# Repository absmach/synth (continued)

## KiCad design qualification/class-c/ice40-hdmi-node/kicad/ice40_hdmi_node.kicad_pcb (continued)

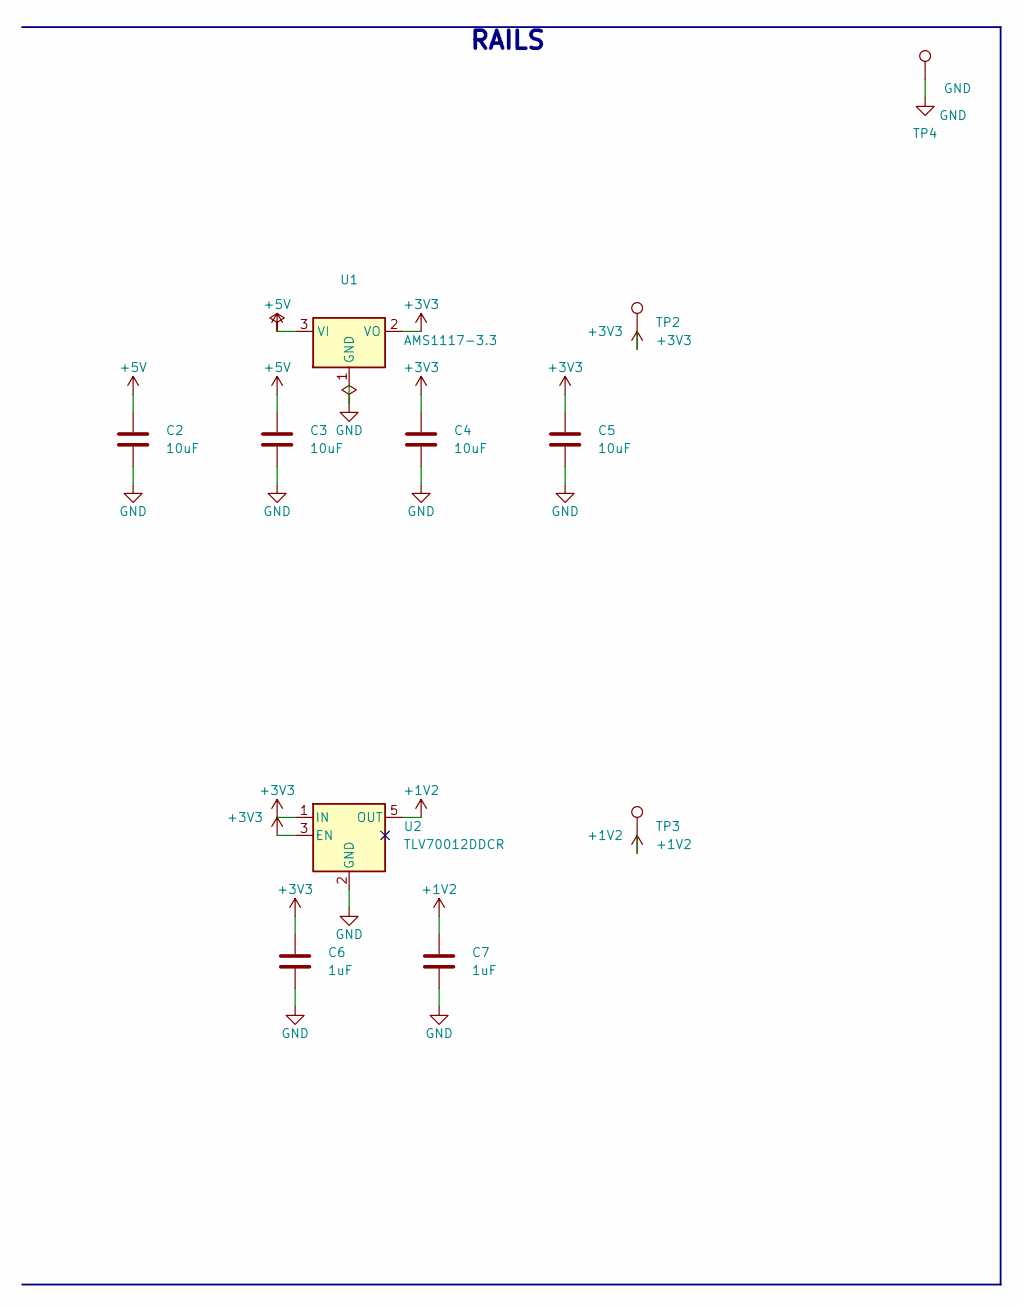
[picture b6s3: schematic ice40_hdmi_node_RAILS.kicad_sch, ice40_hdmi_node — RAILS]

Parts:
C2, C3, C4, C5: 10uF; C_0805_2012Metric
C6, C7: 1uF; C_0603_1608Metric
TP2: +3V3; TestPoint_Pad_D1.5mm
TP3: +1V2; TestPoint_Pad_D1.5mm
TP4: GND; TestPoint_Pad_D1.5mm
U1: AMS1117-3.3; SOT-223-3_TabPin2; MPN AMS1117-3.3; LCSC C6186
U2: TLV70012DDCR; TSOT-23-5; MPN TLV70012DDCR

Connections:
+1V2: C7.1, TP3.1, U2.5 (OUT); also elsewhere on the board
+3V3: C4.1, C5.1, C6.1, TP2.1, U1.2 (VO), U2.1 (IN), U2.3 (EN); also elsewhere on the board
+5V: C2.1, C3.1, U1.3 (VI); also elsewhere on the board
GND: C2.2, C3.2, C4.2, C5.2, C6.2, C7.2, TP4.1, U1.1 (GND), U2.2 (GND); also elsewhere on the board

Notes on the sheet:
RAILS

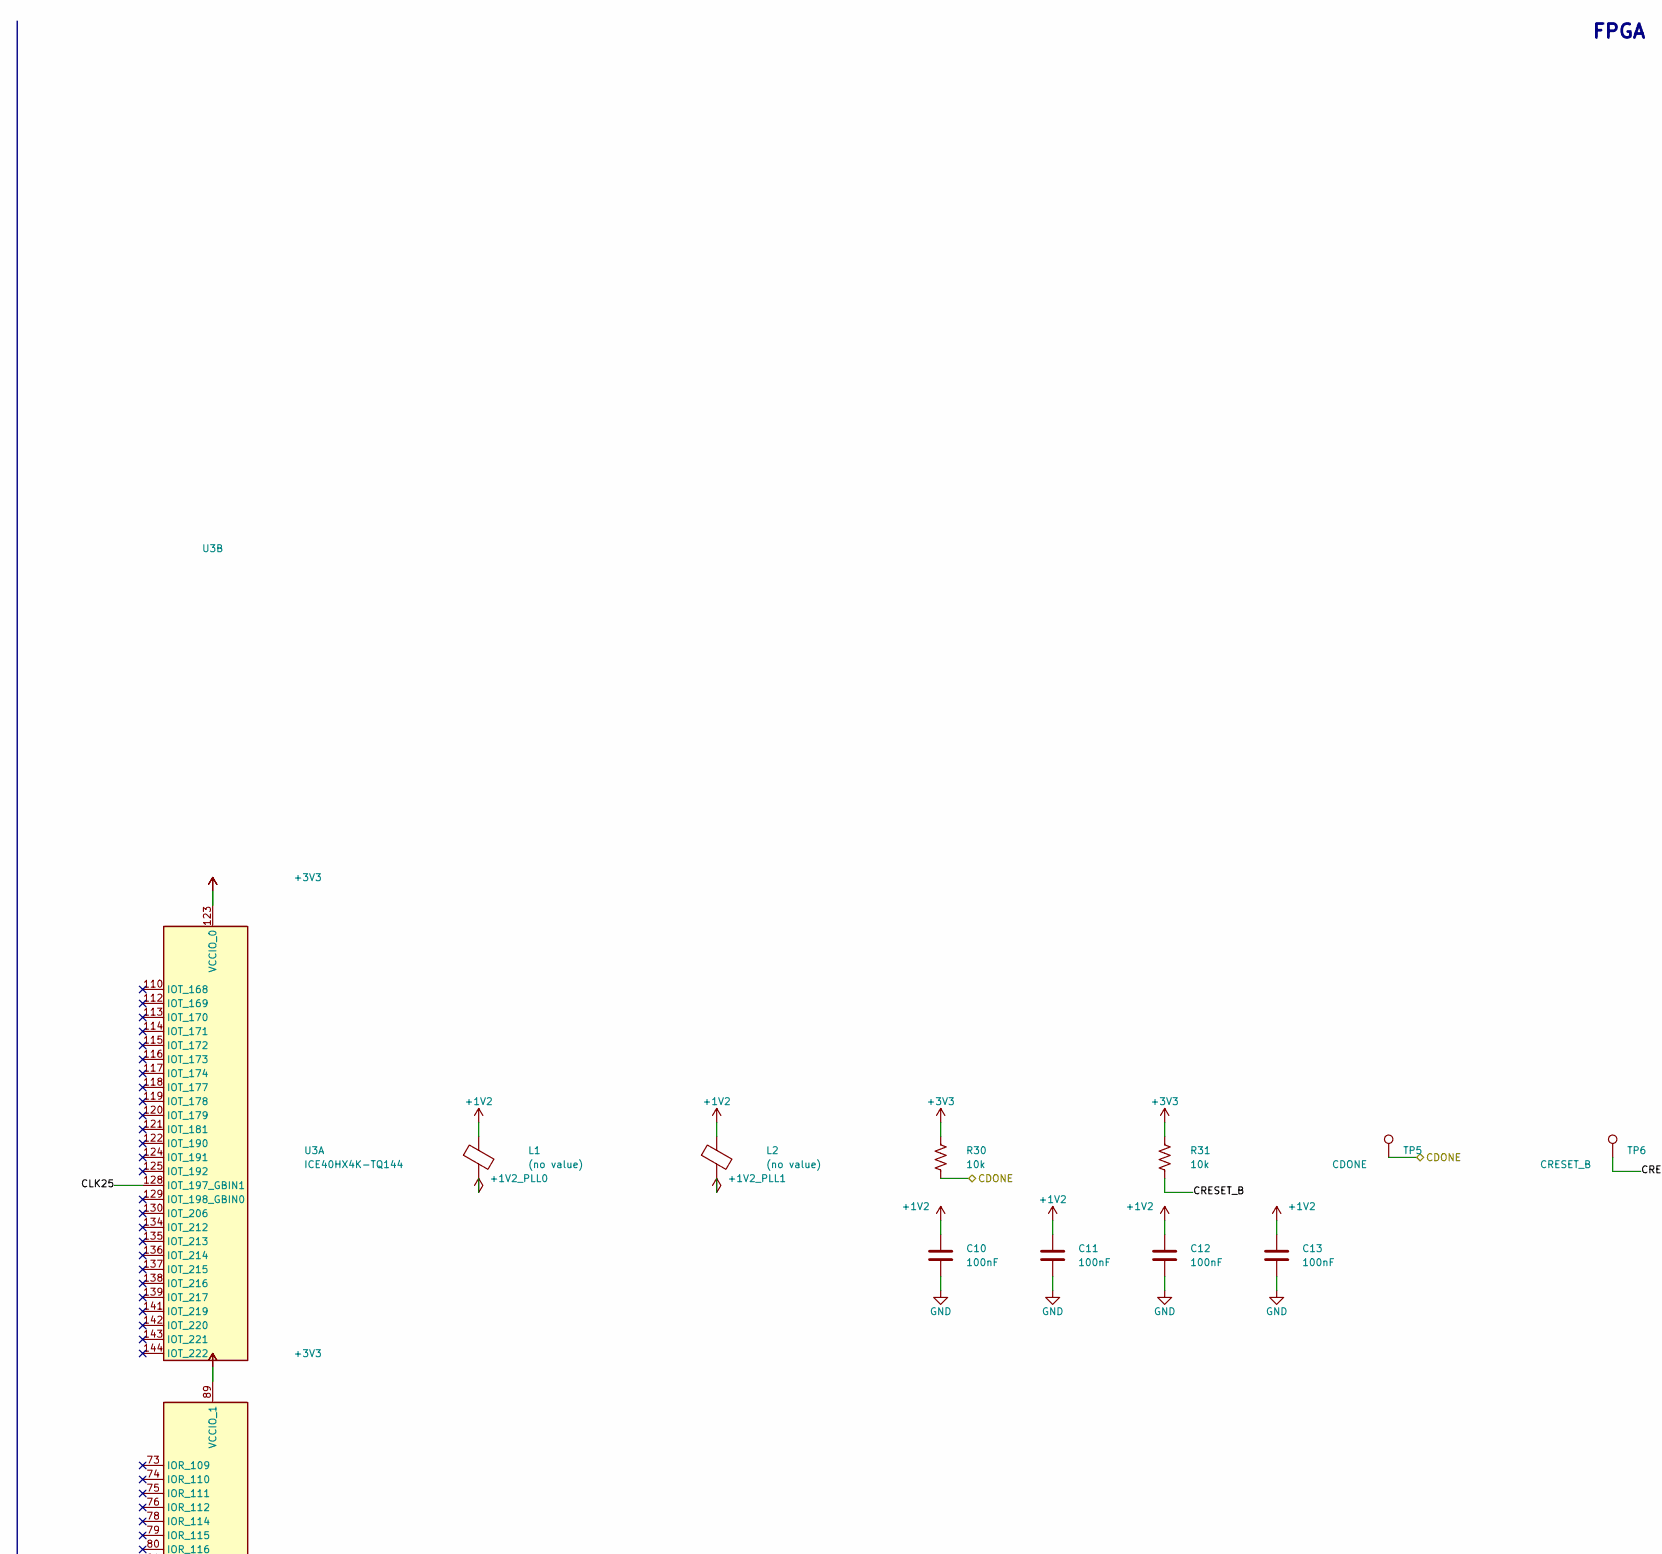
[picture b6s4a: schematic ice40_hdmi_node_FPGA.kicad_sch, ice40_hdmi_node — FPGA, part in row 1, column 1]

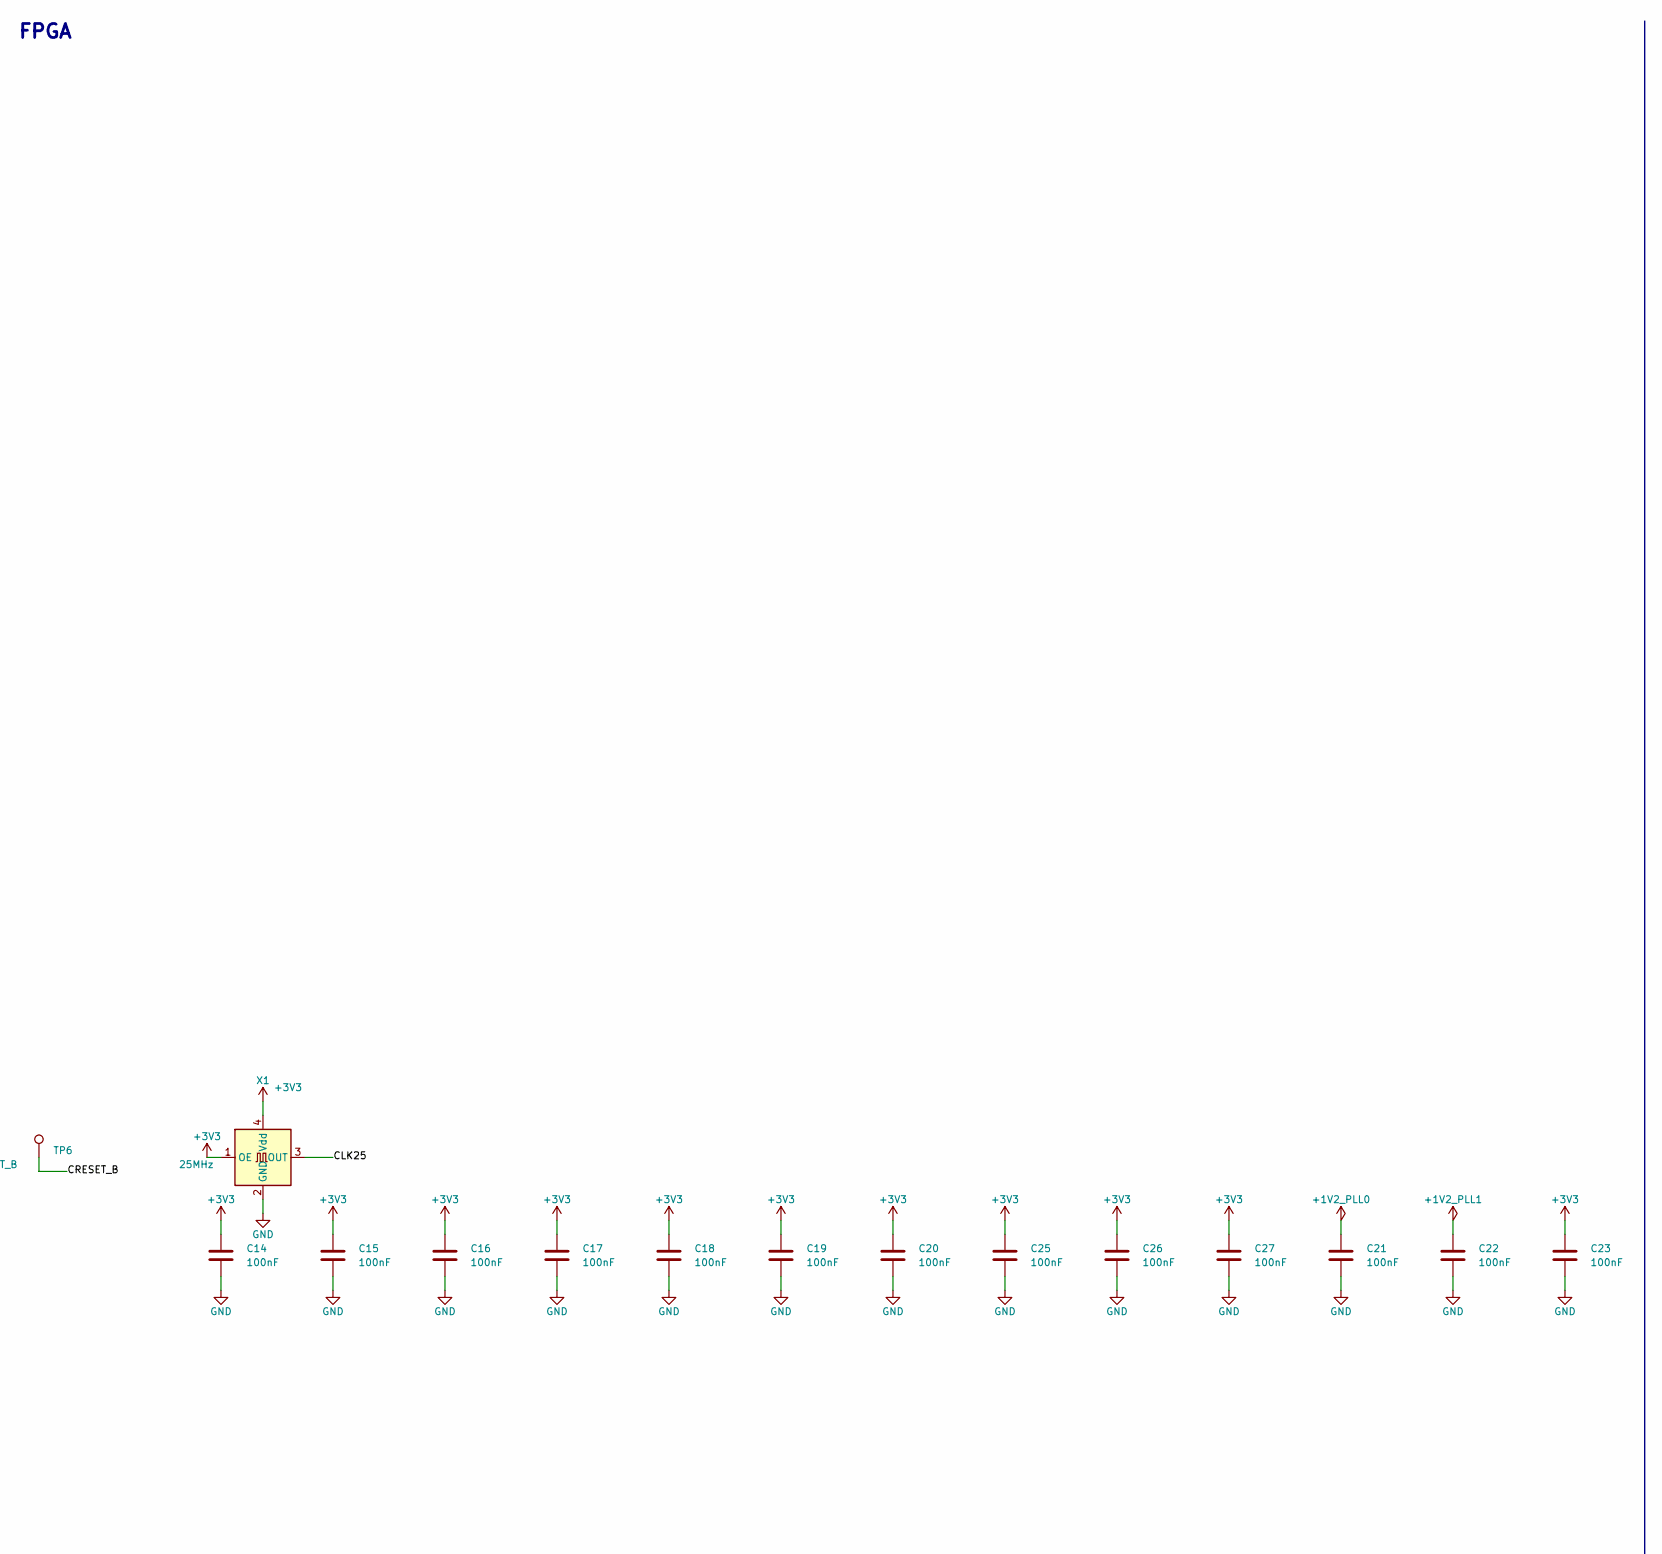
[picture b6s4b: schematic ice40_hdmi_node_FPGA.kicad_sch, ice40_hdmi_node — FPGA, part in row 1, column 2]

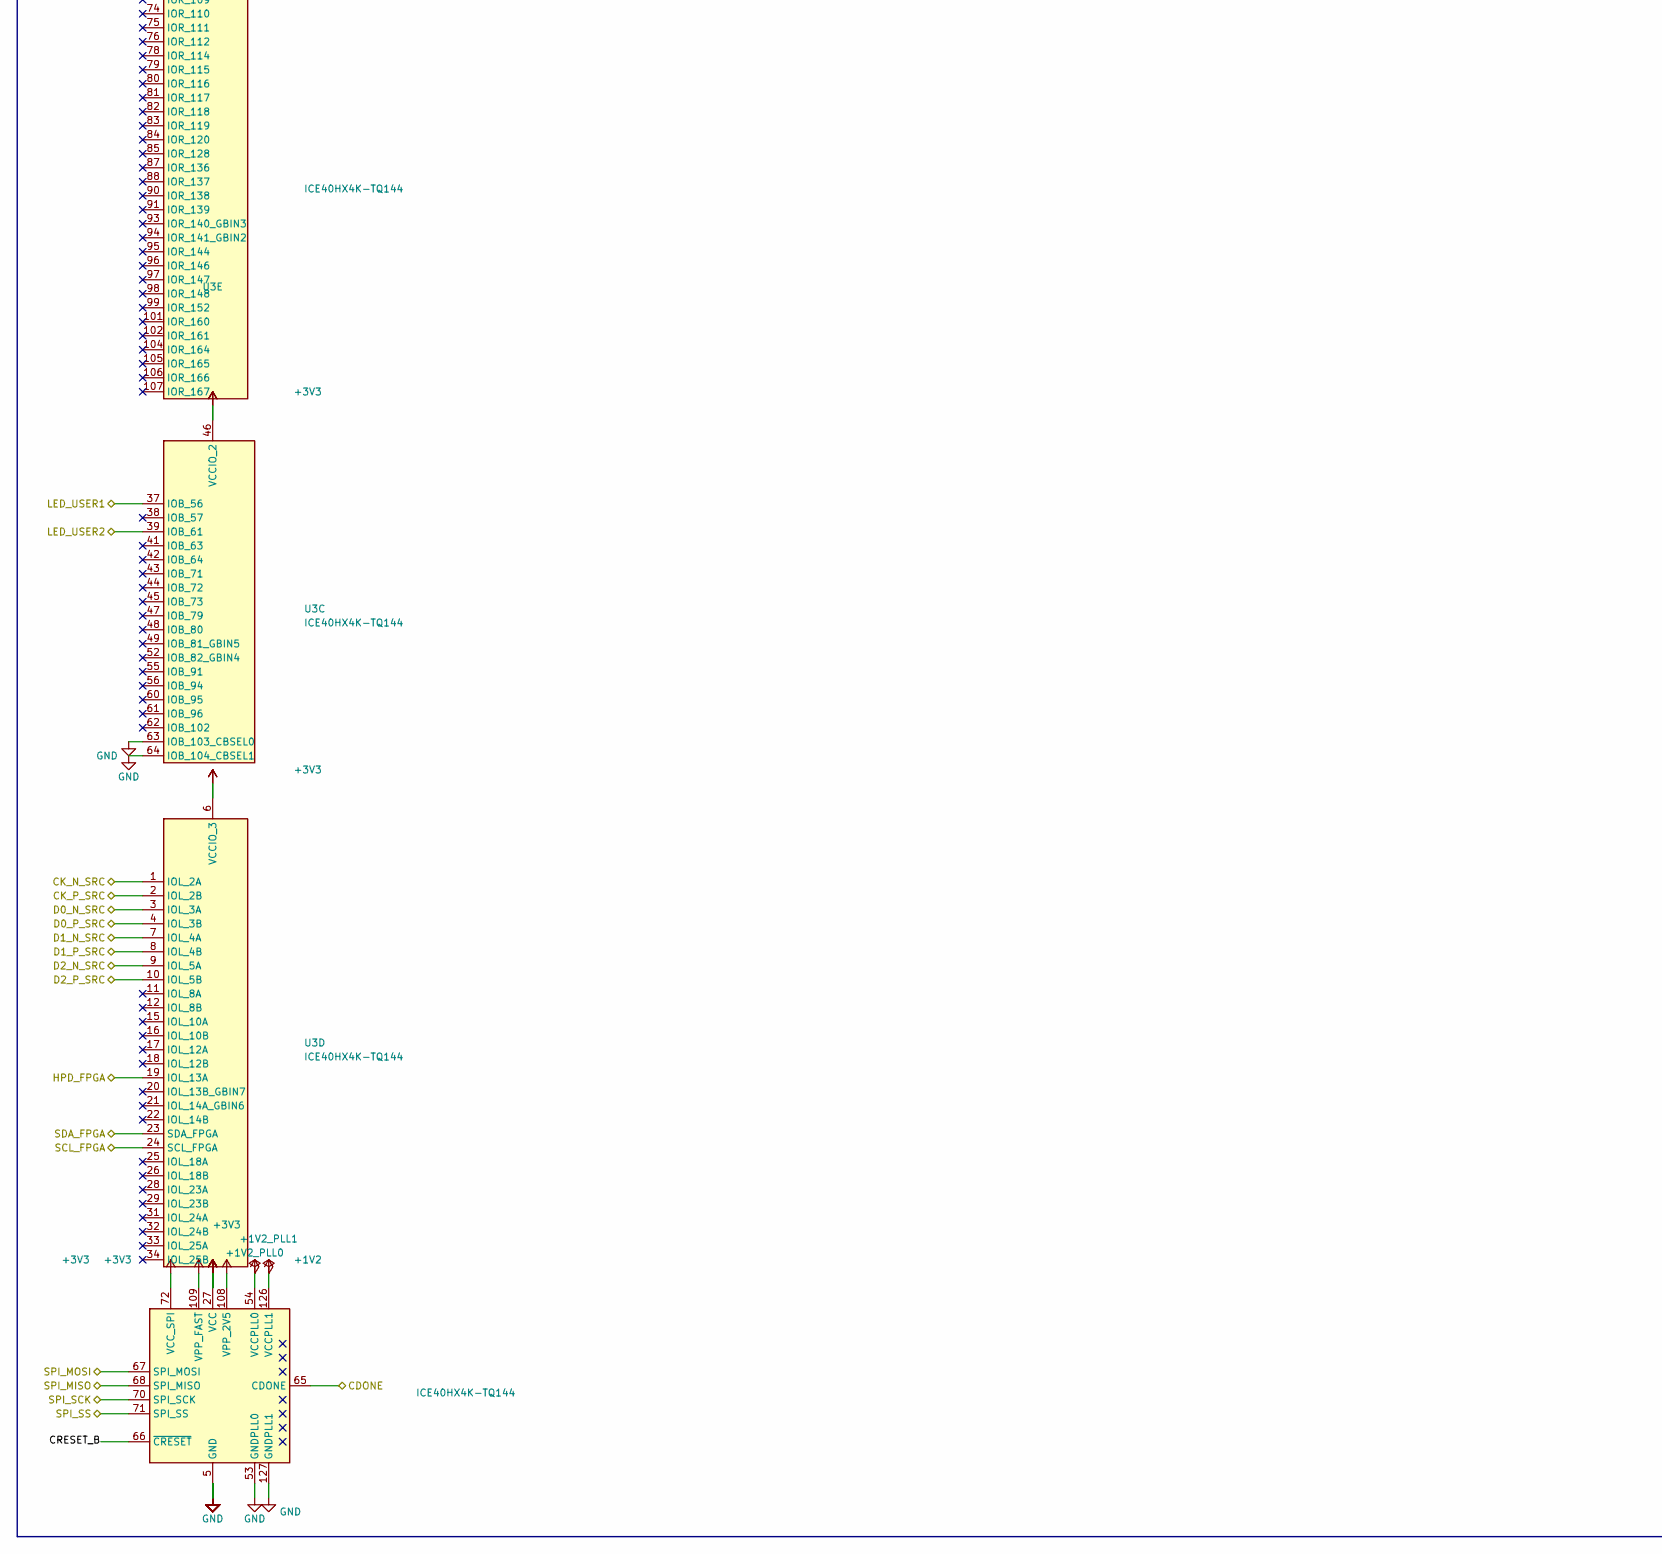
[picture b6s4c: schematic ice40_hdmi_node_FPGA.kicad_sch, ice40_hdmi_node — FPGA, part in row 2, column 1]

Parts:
C10, C11, C12, C13, C14, C15, C16, C17, C18, C19, C20, C21, C22, C23, C25, C26, C27: 100nF; C_0402_1005Metric
L1, L2: (no value); L_0603_1608Metric
R30, R31: 10k; R_0603_1608Metric
TP5: CDONE; TestPoint_Pad_D1.5mm
TP6: CRESET_B; TestPoint_Pad_D1.5mm
U3: ICE40HX4K-TQ144; TQFP-144_20x20mm_P0.5mm; MPN ICE40HX4K-TQ144
X1: 25MHz; Oscillator_SMD_SiT_PQFN-4Pin_5.0x3.2mm

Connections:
+1V2: C10.1, C11.1, C12.1, C13.1, L1.1, L2.1, U3.27 (VCC), U3.40 (VCC), U3.92 (VCC), U3.111 (VCC); also elsewhere on the board
+1V2_PLL0: C21.1, L1.2, U3.54 (VCCPLL0)
+1V2_PLL1: C22.1, L2.2, U3.126 (VCCPLL1)
+3V3: C14.1, C15.1, C16.1, C17.1, C18.1, C19.1, C20.1, C23.1, C25.1, C26.1, C27.1, R30.1, R31.1, U3.6 (VCCIO_3), U3.30 (VCCIO_3), U3.46 (VCCIO_2), U3.57 (VCCIO_2), U3.72 (VCC_SPI), U3.89 (VCCIO_1), U3.100 (VCCIO_1), U3.108 (VPP_2V5), U3.109 (VPP_FAST), U3.123 (VCCIO_0), U3.131 (VCCIO_0), X1.1 (OE), X1.4 (Vdd); also elsewhere on the board
CDONE: R30.2, TP5.1, U3.65 (CDONE); also elsewhere on the board
CK_N_SRC: U3.1 (IOL_2A); also elsewhere on the board
CK_P_SRC: U3.2 (IOL_2B); also elsewhere on the board
CLK25: U3.128 (IOT_197_GBIN1), X1.3 (OUT)
CRESET_B: R31.2, TP6.1, U3.66 (~CRESET)
D0_N_SRC: U3.3 (IOL_3A); also elsewhere on the board
D0_P_SRC: U3.4 (IOL_3B); also elsewhere on the board
D1_N_SRC: U3.7 (IOL_4A); also elsewhere on the board
D1_P_SRC: U3.8 (IOL_4B); also elsewhere on the board
D2_N_SRC: U3.9 (IOL_5A); also elsewhere on the board
D2_P_SRC: U3.10 (IOL_5B); also elsewhere on the board
GND: C10.2, C11.2, C12.2, C13.2, C14.2, C15.2, C16.2, C17.2, C18.2, C19.2, C20.2, C21.2, C22.2, C23.2, C25.2, C26.2, C27.2, U3.5 (GND), U3.13 (GND), U3.14 (GND), U3.53 (GNDPLL0), U3.59 (GND), U3.63 (IOB_103_CBSEL0), U3.64 (IOB_104_CBSEL1), U3.69 (GND), U3.86 (GND), U3.103 (GND), U3.127 (GNDPLL1), U3.132 (GND), U3.140 (GND), X1.2 (GND); also elsewhere on the board
HPD_FPGA: U3.19 (IOL_13A); also elsewhere on the board
LED_USER1: U3.37 (IOB_56); also elsewhere on the board
LED_USER2: U3.39 (IOB_61); also elsewhere on the board
SCL_FPGA: U3.24 (IOL_17B); also elsewhere on the board
SDA_FPGA: U3.23 (IOL_17A); also elsewhere on the board
SPI_MISO: U3.68 (IOB_106_SDI); also elsewhere on the board
SPI_MOSI: U3.67 (IOB_105_SDO); also elsewhere on the board
SPI_SCK: U3.70 (IOB_107_SCK); also elsewhere on the board
SPI_SS: U3.71 (IOB_108_SS); also elsewhere on the board

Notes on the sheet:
FPGA

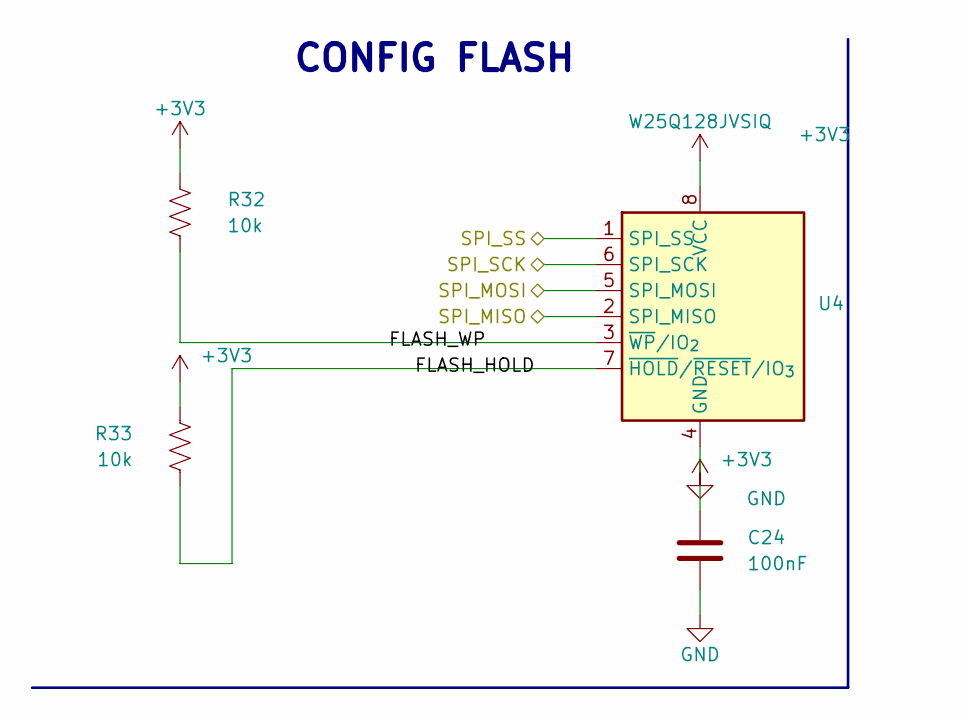
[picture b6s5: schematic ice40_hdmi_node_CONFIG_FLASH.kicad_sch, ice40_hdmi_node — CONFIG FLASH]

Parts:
C24: 100nF; C_0402_1005Metric
R32, R33: 10k; R_0603_1608Metric
U4: W25Q128JVSIQ; SOIC-8_5.3x5.3mm_P1.27mm; MPN W25Q128JVSIQ; LCSC C97521

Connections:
+3V3: C24.1, R32.1, R33.1, U4.8 (VCC); also elsewhere on the board
FLASH_HOLD: R33.2, U4.7 (~HOLD/~RESET/IO_{3})
FLASH_WP: R32.2, U4.3 (~WP/IO_{2})
GND: C24.2, U4.4 (GND); also elsewhere on the board
SPI_MISO: U4.2 (DO/IO_{1}); also elsewhere on the board
SPI_MOSI: U4.5 (DI/IO_{0}); also elsewhere on the board
SPI_SCK: U4.6 (CLK); also elsewhere on the board
SPI_SS: U4.1 (~CS); also elsewhere on the board

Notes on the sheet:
CONFIG FLASH

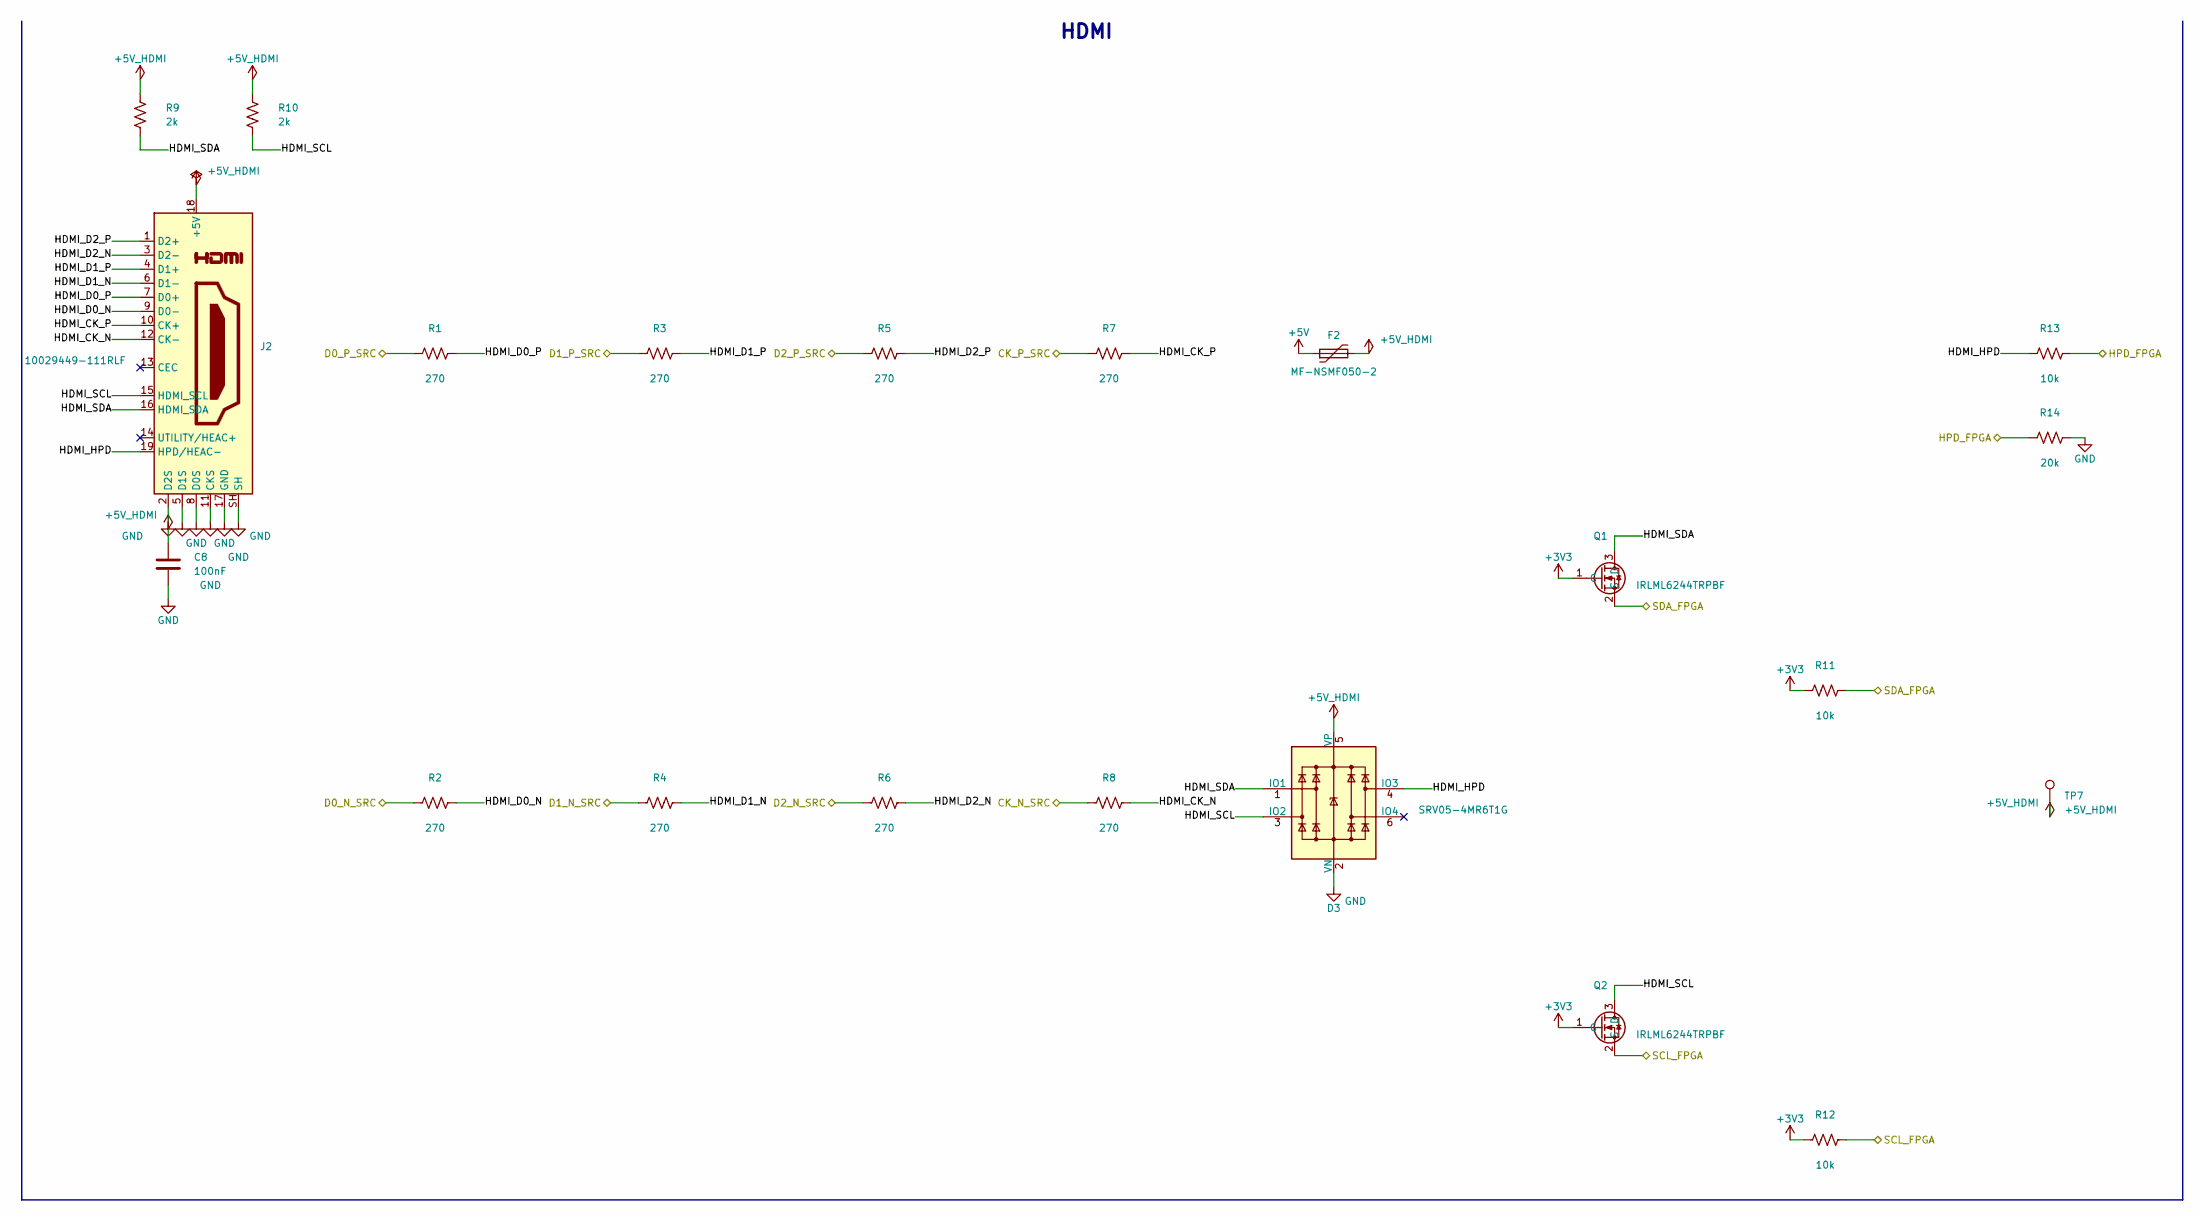
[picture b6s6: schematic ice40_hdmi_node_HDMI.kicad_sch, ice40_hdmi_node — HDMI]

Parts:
C8: 100nF; C_0603_1608Metric
D3: SRV05-4MR6T1G; SOT-23-6; MPN SRV05-4MR6T1G
F2: MF-NSMF050-2; Fuse_1206_3216Metric; MPN MF-NSMF050-2; LCSC C75464
J2: 10029449-111RLF; HDMI_A_Amphenol_10029449-x01xLF_Horizontal; MPN 10029449-111RLF
Q1, Q2: IRLML6244TRPBF; SOT-23; MPN IRLML6244TRPBF; LCSC C143946
R1, R2, R3, R4, R5, R6, R7, R8: 270; R_0603_1608Metric
R9, R10: 2k; R_0603_1608Metric
R11, R12, R13: 10k; R_0603_1608Metric
R14: 20k; R_0603_1608Metric
TP7: +5V_HDMI; TestPoint_Pad_D1.5mm

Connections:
+3V3: Q1.1 (G), Q2.1 (G), R11.1, R12.1; also elsewhere on the board
+5V: F2.1; also elsewhere on the board
+5V_HDMI: C8.1, D3.5 (VP), F2.2, J2.18 (+5V), R9.1, R10.1, TP7.1
CK_N_SRC: R8.1; also elsewhere on the board
CK_P_SRC: R7.1; also elsewhere on the board
D0_N_SRC: R2.1; also elsewhere on the board
D0_P_SRC: R1.1; also elsewhere on the board
D1_N_SRC: R4.1; also elsewhere on the board
D1_P_SRC: R3.1; also elsewhere on the board
D2_N_SRC: R6.1; also elsewhere on the board
D2_P_SRC: R5.1; also elsewhere on the board
GND: C8.2, D3.2 (VN), J2.2 (D2S), J2.5 (D1S), J2.8 (D0S), J2.11 (CKS), J2.17 (GND), J2.SH, R14.2; also elsewhere on the board
HDMI_CK_N: J2.12 (CK-), R8.2
HDMI_CK_P: J2.10 (CK+), R7.2
HDMI_D0_N: J2.9 (D0-), R2.2
HDMI_D0_P: J2.7 (D0+), R1.2
HDMI_D1_N: J2.6 (D1-), R4.2
HDMI_D1_P: J2.4 (D1+), R3.2
HDMI_D2_N: J2.3 (D2-), R6.2
HDMI_D2_P: J2.1 (D2+), R5.2
HDMI_HPD: D3.4 (IO3), J2.19 (HPD/HEAC-), R13.1
HDMI_SCL: D3.3 (IO2), J2.15 (SCL), Q2.3 (D), R10.2
HDMI_SDA: D3.1 (IO1), J2.16 (SDA), Q1.3 (D), R9.2
HPD_FPGA: R13.2, R14.1; also elsewhere on the board
SCL_FPGA: Q2.2 (S), R12.2; also elsewhere on the board
SDA_FPGA: Q1.2 (S), R11.2; also elsewhere on the board

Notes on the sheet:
HDMI

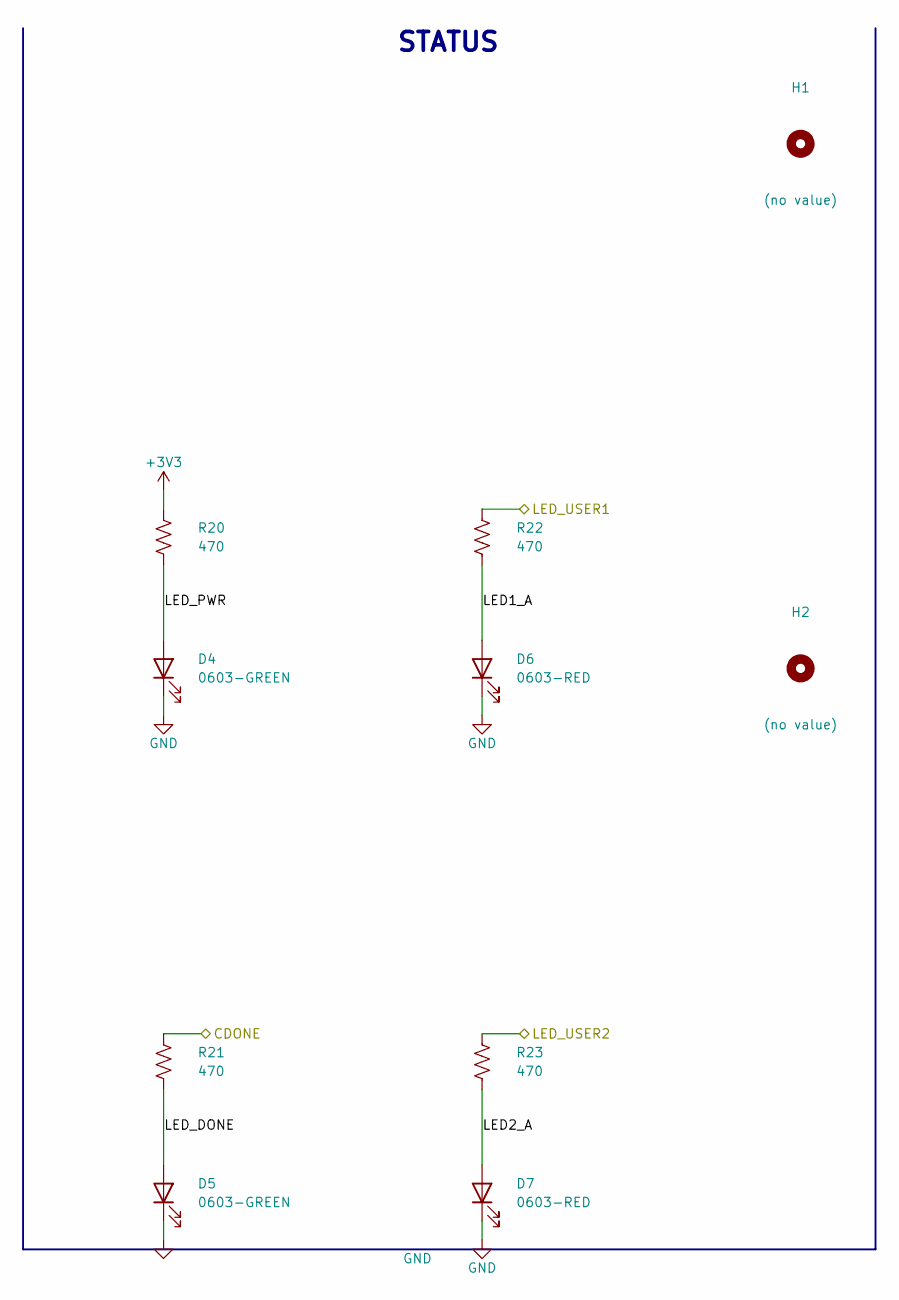
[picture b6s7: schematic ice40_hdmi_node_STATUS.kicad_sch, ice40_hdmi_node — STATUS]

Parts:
D4, D5: 0603-GREEN; LED_0603_1608Metric; MPN 0603-GREEN; LCSC C72043
D6, D7: 0603-RED; LED_0603_1608Metric; MPN 0603-RED; LCSC C2286
H1, H2: (no value); MountingHole_2.5mm
R20, R21, R22, R23: 470; R_0603_1608Metric

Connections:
+3V3: R20.1; also elsewhere on the board
CDONE: R21.1; also elsewhere on the board
GND: D4.1 (K), D5.1 (K), D6.1 (K), D7.1 (K); also elsewhere on the board
LED1_A: D6.2 (A), R22.2
LED2_A: D7.2 (A), R23.2
LED_DONE: D5.2 (A), R21.2
LED_PWR: D4.2 (A), R20.2
LED_USER1: R22.1; also elsewhere on the board
LED_USER2: R23.1; also elsewhere on the board

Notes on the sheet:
STATUS

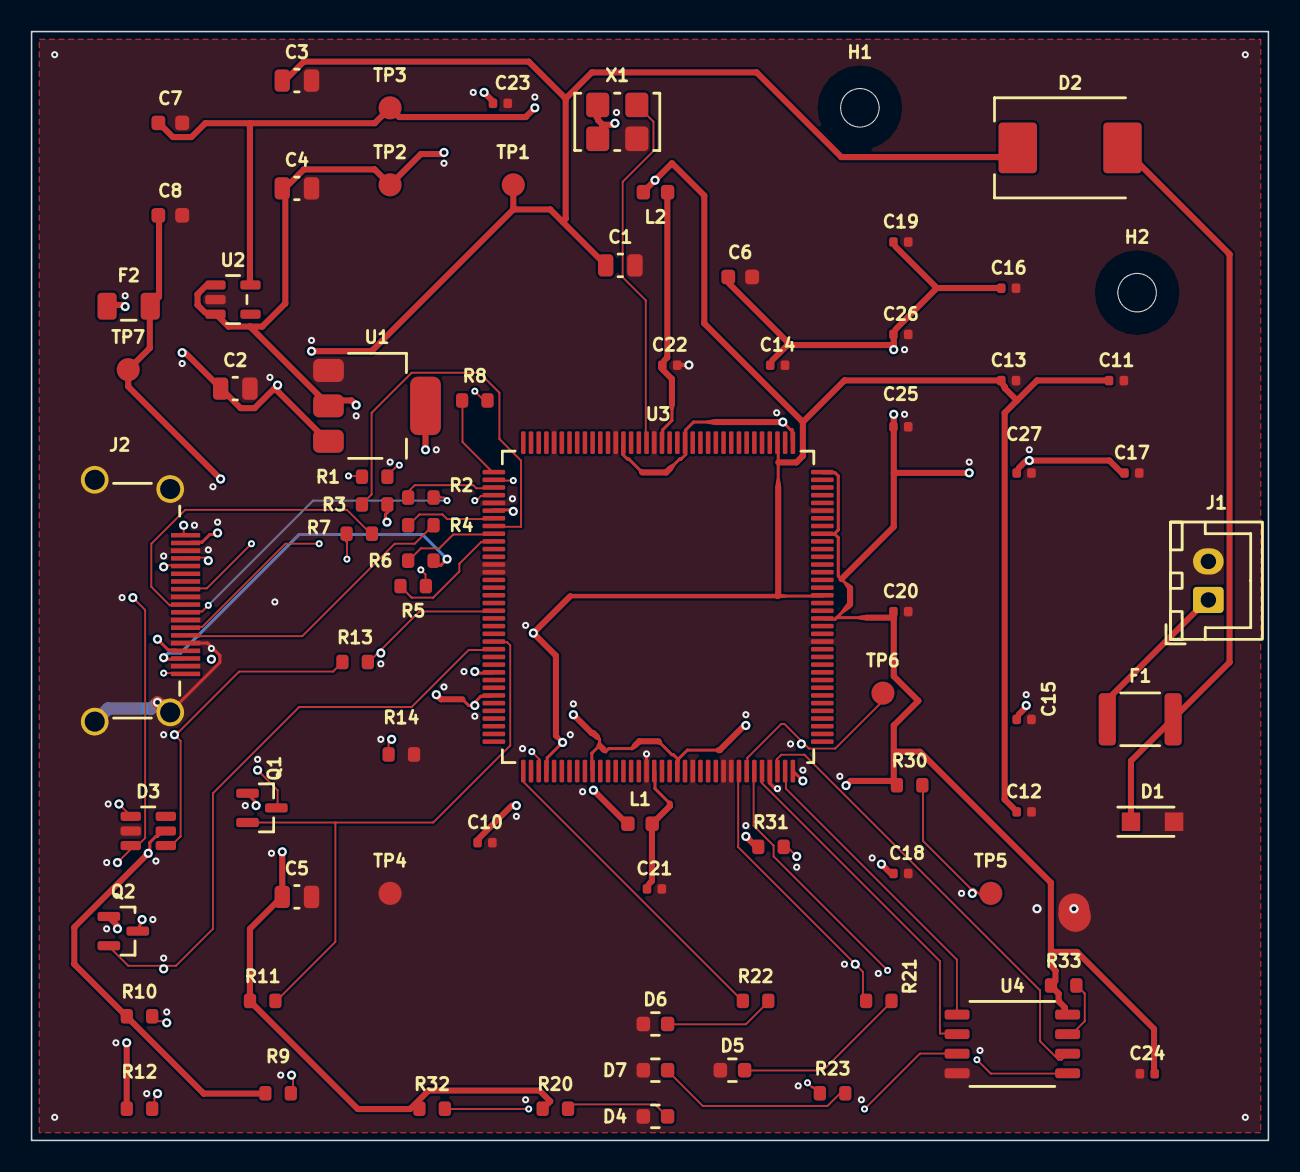
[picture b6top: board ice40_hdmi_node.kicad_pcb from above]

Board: 6 copper layers, 80.3 x 72.0 mm, 77 parts (0 on the bottom side), 46 nets.
